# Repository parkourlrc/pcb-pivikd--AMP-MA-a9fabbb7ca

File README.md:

# Project Status

   **AMP-MA is currently in the early development phase and is considered unstable. The first stable release is scheduled for Q4 2026**
   
   **The project is currently in the pre-alpha stage – creating the first prototype**

# AMP-MA (AMP Modus Aequale)

AMP-MA (standing for Modus Aequale, signifying a rhythmic, ideal tone and modular structure) is an open-source, transistor-based guitar combo amplifier project. It is designed to bridge the gap between solid-state reliability and the organic, harmonic richness of vacuum tube sound.

The project focuses on a modular architecture, originally developed as a high-fidelity upgrade for the **Epiphone 15C** PCB. By utilizing independent blocks, AMP-MA allows for seamless customization and easier adaptation to various amp enclosures.

This project is designed and maintained by: [Danylo Pyvovarov](https://github.com/pivikd).

   1. [Key Features](#key-features)
   1. [Signal Chain](#signal-chain)
   1. [Integrated Tone Stacks](#integrated-tone-stacks)
<!-- 1. [Integrated Effects Modules](#integrated-effects-modules) -->
## Key Features
   - **Tube-like Architecture**: Uses **Mu-amp** based cascades with **2SK30A** transistors to achieve a warm, organic sound and harmonic saturation that mimics vacuum tube behavior.

   - **Dual Input Support**: Designed to handle two guitars simultaneously.

   - **Legendary Tone Stacks**: Features a 3-band EQ based on the classic tone stacks([Integrated Tone Stacks](#integrated-tone-stacks)).

   - **Integrated Compression**: Built-in compressor block based on the vintage **Ibanez CP835** circuitry.

   <!-- - **Modular Design**: Optimized for easy integration into different amp cabinets or for swapping internal effect modules. -->

## Signal Chain
   1. Input buffer
   1. Preamp ([Mu-AMP](https://www.muzique.com/amz/mini.htm))
   1. Compressor ([Ibanez CP835](https://www.scribd.com/document/976348354/Ibanez-CP835-Schematic))
   1. Tone Stack
   1. Recovery Stage
   1. Power Amp ([LM1875](https://www.ti.com/lit/ds/symlink/lm1875.pdf))

<!-- ## Integrated Effects Modules
|       Effect      |   based on   |  Status  |
|-------------------|--------------|---------|
| Compressor        | Ibanez CP835 |  done   |
<!-- | Over Drive        | Boss OD3     | planned  |
| Chorus            | Boss Ch1     | planned  | --> 

## Integrated Tone Stacks
   - Fender Treble-Middle-Bass
   - Marshall ([JCM900 2100 SL-X](https://stompboxelectronics.com/2023/12/16/the-marshall-tone-stacks/))
   - Dumble Rock

      Own:
   - TS0 (based on Marshall JCM900 2100 SL-x)
   - TS1 (based on Dumble Rock)

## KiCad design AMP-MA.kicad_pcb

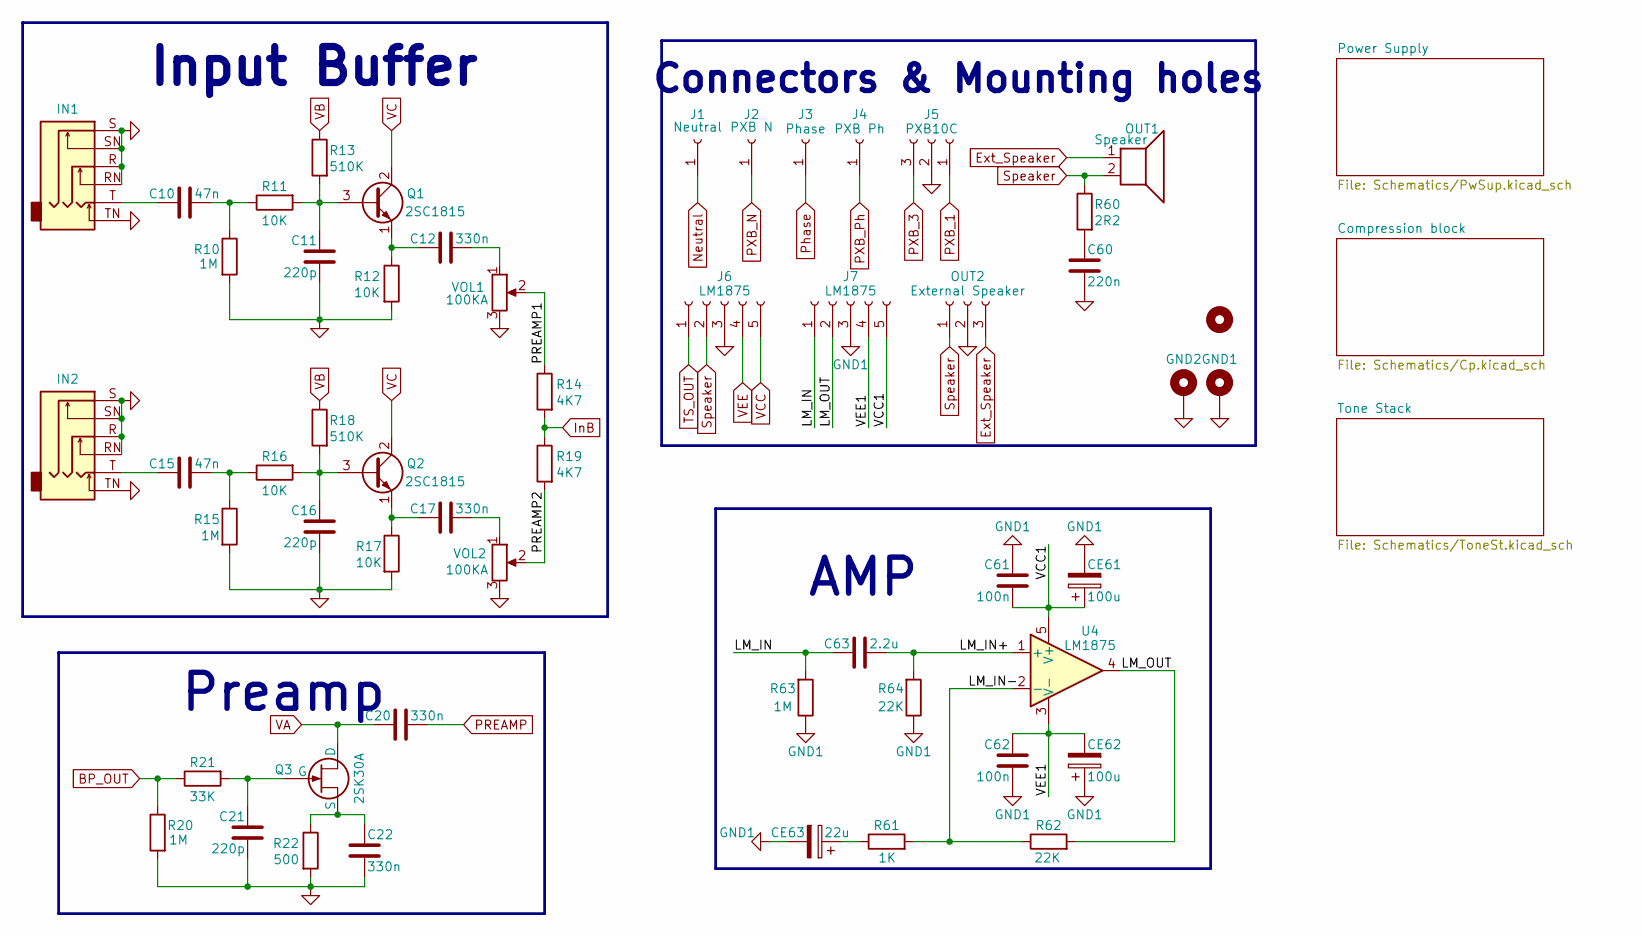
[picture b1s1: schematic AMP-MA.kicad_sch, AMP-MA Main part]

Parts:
C10, C15: 47n; C_disc_D7_W2.5_P5
C11, C16, C21: 220p; C_disc_D7_W2.5_P5
C12, C17, C20, C22: 330n; C_disc_D7_W2.5_P5
C60: 220n; C_disc_D7_W2.5_P5
C61, C62: 100n; C_disc_D7_W2.5_P5
C63: 2.2u; C_disc_D7_W2.5_P5
CE61, CE62: 100u; CP_Radial_D6.3mm_P2.50mm
CE63: 22u; CP_Radial_D5.0mm_P2.50mm
GND1, GND2: MountingHole_Pad; MountingHole_2.2mm_M2_DIN965_Pad
H2: MountingHole; MountingHole_2.2mm_M2
IN1, IN2: Jack_3_6pin
J1: Neutral; connector
J2: PXB N; connector
J3: Phase
J4: PXB Ph
J5: PXB10C; JST_XH_B3B-XH-A_1x03_P2.50mm_Vertical
J6, J7: LM1875; JST_XH_B5B-XH-A_1x05_P2.50mm_Vertical
OUT1: Speaker; PinSocket_1x02_P2.54mm_Vertical
OUT2: External Speaker; JST_XH_B3B-XH-A_1x03_P2.50mm_Vertical
Q1, Q2: 2SC1815; TO-92_Inline_Wide
Q3: 2SK30A; TO-92_Inline_Wide
R10, R15, R20, R63: 1M; R_Axial_DIN0207_L6.3mm_D2.5mm_P10.16mm_Horizontal
R11, R12, R16, R17: 10K; R_Axial_DIN0207_L6.3mm_D2.5mm_P10.16mm_Horizontal
R13, R18: 510K; R_Axial_DIN0207_L6.3mm_D2.5mm_P10.16mm_Horizontal
R14, R19: 4K7; R_Axial_DIN0207_L6.3mm_D2.5mm_P10.16mm_Horizontal
R21: 33K; R_Axial_DIN0207_L6.3mm_D2.5mm_P10.16mm_Horizontal
R22: 500; R_Axial_DIN0207_L6.3mm_D2.5mm_P10.16mm_Horizontal
R60: 2R2; R_Axial_DIN0207_L6.3mm_D2.5mm_P10.16mm_Horizontal
R61: 1K; R_Axial_DIN0207_L6.3mm_D2.5mm_P10.16mm_Horizontal
R62, R64: 22K; R_Axial_DIN0207_L6.3mm_D2.5mm_P10.16mm_Horizontal
U4: LM1875; TO-220-5_P3.4x3.7mm_StaggerOdd_Lead3.8mm_Vertical
VOL1, VOL2: 100KA; potentiometer

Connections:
/LM_IN: C63.1, J7.1, R63.2
/LM_IN+: C63.2, R64.2, U4.1 (+)
/LM_IN-: R61.2, R62.1, U4.2 (-)
/LM_OUT: J7.2, R62.2, U4.4
/PREAMP1: R14.1, VOL1.2
/PREAMP2: R19.2, VOL2.2
/VCC1: C61.2, CE61.1, J7.5, U4.5 (V+)
/VEE1: C62.1, CE62.2, J7.4, U4.3 (V-)
BP_OUT: R20.1, R21.1; also elsewhere on the board
Ext_Speaker: OUT1.1, OUT2.3
GND: C11.1, C16.1, C21.1, C22.1, C60.2, GND1.1 (1_1), GND2.1 (1_1), IN1.R, IN1.RN, IN1.S, IN1.SN, IN1.TN, IN2.R, IN2.RN, IN2.S, IN2.SN, IN2.TN, J5.2, J6.3, OUT2.2, R10.2, R12.2, R15.2, R17.2, R20.2, R22.2, VOL1.3, VOL2.3; also elsewhere on the board
GND1: C61.1, C62.2, CE61.2, CE62.1, CE63.2, J7.3, R63.1, R64.1
InB: R14.2, R19.1; also elsewhere on the board
unnamed: C10.1, IN1.T
unnamed: C10.2, R10.1, R11.1
unnamed: C12.2, VOL1.1
unnamed: C15.1, IN2.T
unnamed: C15.2, R15.1, R16.1
unnamed: C17.2, VOL2.1
unnamed: C60.1, R60.2
unnamed: CE63.1, R61.1
unnamed: C11.2, Q1.3 (B), R11.2, R13.2
unnamed: C12.1, Q1.1 (E), R12.1
unnamed: C16.2, Q2.3 (B), R16.2, R18.2
unnamed: C17.1, Q2.1 (E), R17.1
unnamed: C21.2, Q3.2 (G), R21.2
unnamed: C22.2, Q3.3 (S), R22.1
Neutral: J1.1 (Pin_1_1); also elsewhere on the board
PREAMP: C20.2; also elsewhere on the board
PXB_1: J5.1; also elsewhere on the board
PXB_3: J5.3; also elsewhere on the board
PXB_N: J2.1 (Pin_1_1); also elsewhere on the board
Speaker: J6.2, OUT1.2, OUT2.1, R60.1
TS_OUT: J6.1; also elsewhere on the board
VA: C20.1, Q3.1 (D); also elsewhere on the board
VB: R13.1, R18.1; also elsewhere on the board
VC: Q1.2 (C), Q2.2 (C); also elsewhere on the board
VCC: J6.5; also elsewhere on the board
VEE: J6.4; also elsewhere on the board

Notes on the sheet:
Preamp
Connectors & Mounting holes
AMP
Input Buffer

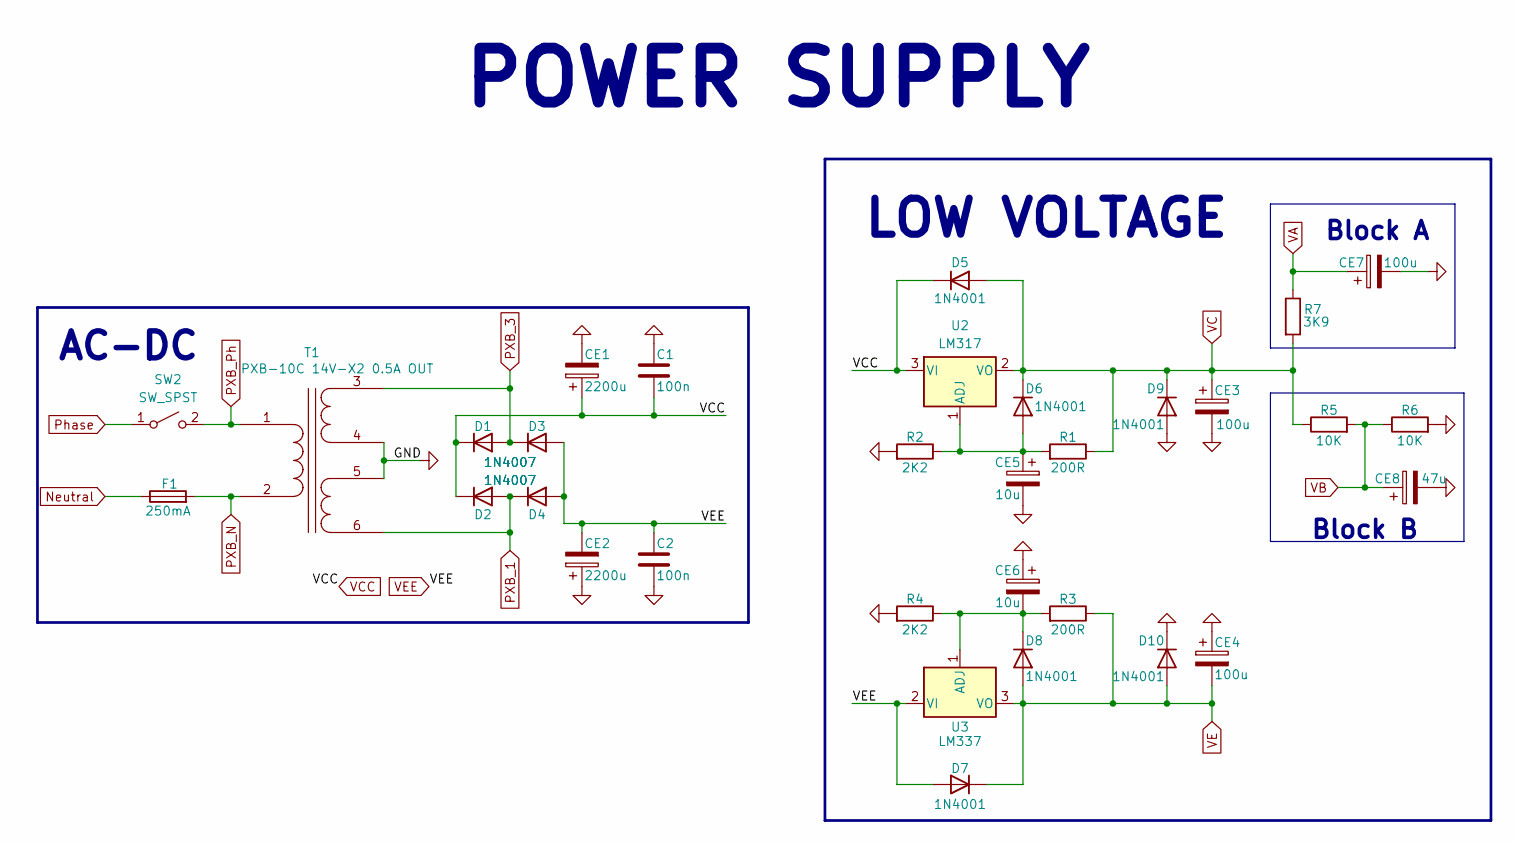
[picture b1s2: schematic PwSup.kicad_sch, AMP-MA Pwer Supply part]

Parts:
C1, C2: 100n; C_disc_D7_W2.5_P5
CE1, CE2: 2200u; CP_Radial_D16.0mm_P7.50mm
CE3, CE4, CE7: 100u; CP_Radial_D6.3mm_P2.50mm
CE5, CE6: 10u; CP_Radial_D5.0mm_P2.50mm
CE8: 47u; CP_Radial_D5.0mm_P2.50mm
D1, D2, D3, D4: 1N4007; D_DO-41_SOD81_P10.16mm_Horizontal
D5, D6, D7, D8, D9, D10: 1N4001; D_DO-41_SOD81_P10.16mm_Horizontal
F1: 250mA; Fuseholder_Clip-5x20mm_Littelfuse_520_Inline_P20.50x5.80mm_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
R1, R3: 200R; R_Axial_DIN0207_L6.3mm_D2.5mm_P10.16mm_Horizontal
R2, R4: 2K2; R_Axial_DIN0207_L6.3mm_D2.5mm_P10.16mm_Horizontal
R5, R6: 10K; R_Axial_DIN0207_L6.3mm_D2.5mm_P10.16mm_Horizontal
R7: 3K9; R_Axial_DIN0207_L6.3mm_D2.5mm_P10.16mm_Horizontal
SW2: SW_SPST
T1: PXB-10C 14V-X2 0.5A OUT
U2: LM317; TO-220-3_Horizontal_TabDown
U3: LM337; TO-220-3_Horizontal_TabDown

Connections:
GND: C1.2, C2.2, CE1.2, CE2.1, CE3.2, CE4.1, CE5.2, CE6.1, CE7.2, CE8.2, D9.2 (A), D10.1 (K), R2.2, R4.2, R6.2, T1.4 (SB), T1.5 (SC); also elsewhere on the board
unnamed: CE5.1, D6.2 (A), R1.2, R2.1, U2.1 (ADJ)
unnamed: CE6.2, D8.1 (K), R3.2, R4.1, U3.1 (ADJ)
unnamed: SW2.2 (B), T1.1 (AA)
Neutral: F1.1; also elsewhere on the board
PXB_1: D2.2 (A), D4.1 (K), T1.6 (SD); also elsewhere on the board
PXB_3: D1.2 (A), D3.1 (K), T1.3 (SA); also elsewhere on the board
PXB_N: F1.2, T1.2 (AB); also elsewhere on the board
VA: CE7.1, R7.1; also elsewhere on the board
VB: CE8.1, R5.2, R6.1; also elsewhere on the board
VC: CE3.1, D5.2 (A), D6.1 (K), D9.1 (K), R1.1, R5.1, R7.2, U2.2 (VO); also elsewhere on the board
VCC: C1.1, CE1.1, D1.1 (K), D2.1 (K), D5.1 (K), U2.3 (VI); also elsewhere on the board
VE: CE4.2, D7.1 (K), D8.2 (A), D10.2 (A), R3.1, U3.3 (VO); also elsewhere on the board
VEE: C2.1, CE2.2, D3.2 (A), D4.2 (A), D7.2 (A), U3.2 (VI); also elsewhere on the board

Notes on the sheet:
AC-DC
Block A
Block B
LOW VOLTAGE
POWER SUPPLY

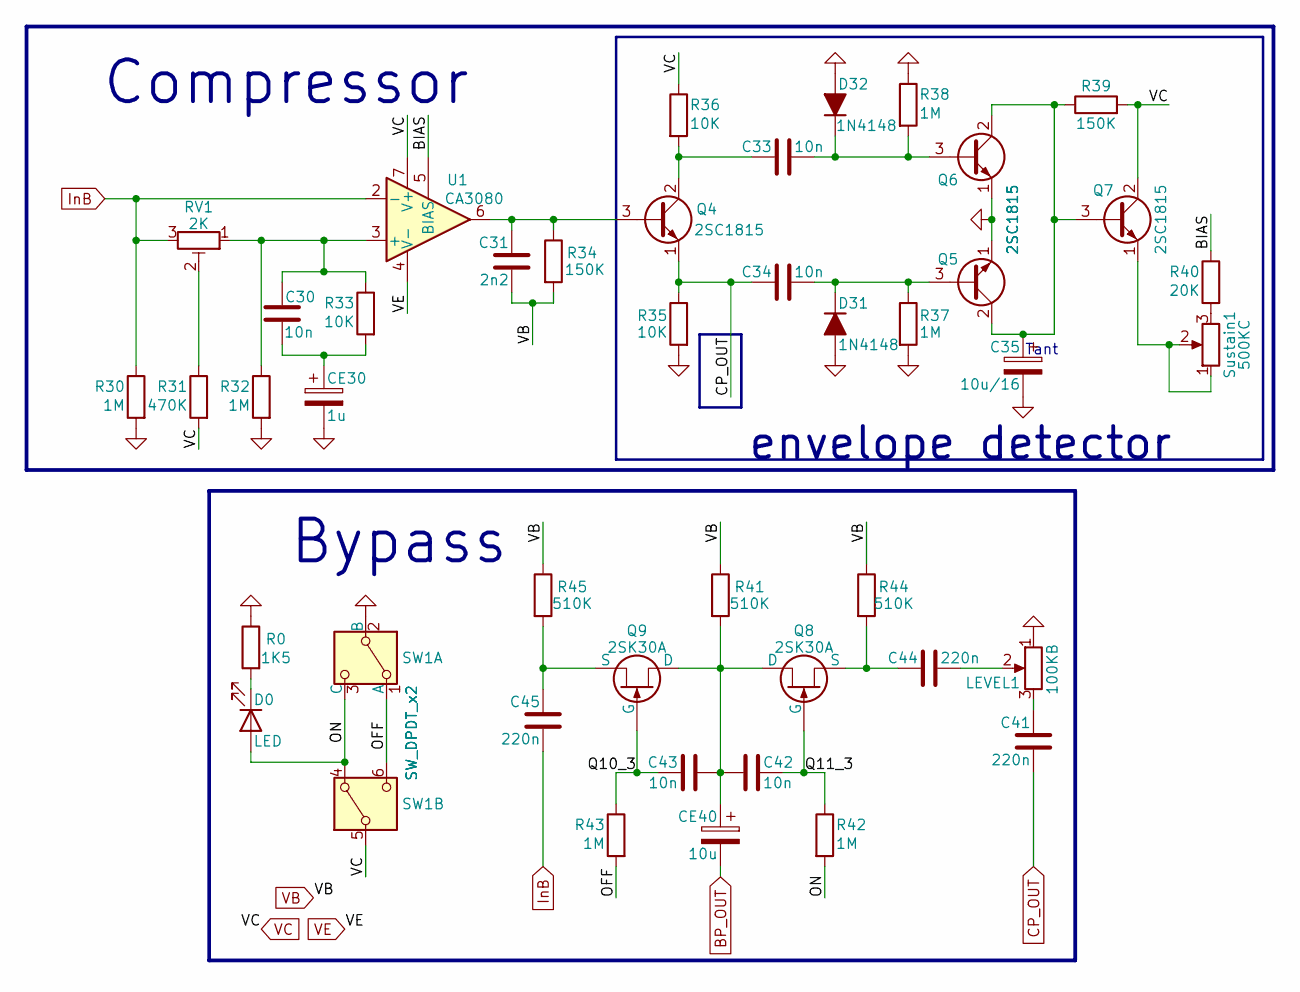
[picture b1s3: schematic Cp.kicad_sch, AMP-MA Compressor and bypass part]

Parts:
C30: 10n; C_disc_D7_W2.5_P5
C31: 2n2; C_Disc_D4.3_W1.9_P5.00
C33, C34, C42, C43: 10n; C_Disc_D4.3_W1.9_P5.00
C35: 10u/16; CP_Radial_Tantal_D5.5mm_P2.50mm
C41, C44, C45: 220n; C_disc_D7_W2.5_P5
CE30: 1u; CP_Radial_D4.0mm_P2.00mm
CE40: 10u; CP_Radial_D5.0mm_P2.50mm
D0: LED; LED_D3.0mm_Horizontal_O6.35mm_Z6.0mm
D31, D32: 1N4148; D_DO-35_SOD27_P7.62mm_Horizontal
LEVEL1: 100KB; Potentiometer_Bourns_3296W_Vertical
Q4, Q5, Q6, Q7: 2SC1815; TO-92_Inline_Wide
Q8, Q9: 2SK30A; TO-92_Inline_Wide
R0: 1K5; R_Axial_DIN0207_L6.3mm_D2.5mm_P10.16mm_Horizontal
R30, R32, R37, R38, R42, R43: 1M; R_Axial_DIN0207_L6.3mm_D2.5mm_P10.16mm_Horizontal
R31: 470K; R_Axial_DIN0207_L6.3mm_D2.5mm_P10.16mm_Horizontal
R33, R35, R36: 10K; R_Axial_DIN0207_L6.3mm_D2.5mm_P10.16mm_Horizontal
R34, R39: 150K; R_Axial_DIN0207_L6.3mm_D2.5mm_P10.16mm_Horizontal
R40: 20K; R_Axial_DIN0207_L6.3mm_D2.5mm_P10.16mm_Horizontal
R41, R44, R45: 510K; R_Axial_DIN0207_L6.3mm_D2.5mm_P10.16mm_Horizontal
RV1: 2K; Potentiometer_Bourns_3296W_Vertical
SW1: SW_DPDT_x2; SW DPDT
Sustain1: 500KC; potentiometer
U1: CA3080; DIP-8_W7.62mm

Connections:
/Compression block/BIAS: R40.1, U1.5 (BIAS)
/Compression block/OFF: R43.2, SW1.1 (A), SW1.6 (C)
/Compression block/ON: D0.2 (A), R42.2, SW1.3 (C), SW1.4 (A)
/Compression block/Q10_3: C43.2, Q9.2 (G), R43.1
/Compression block/Q11_3: C42.1, Q8.2 (G), R42.1
BP_OUT: CE40.2; also elsewhere on the board
CP_OUT: C34.1, C41.1, Q4.1 (E), R35.1
GND: C35.2, CE30.2, D31.2 (A), D32.2 (A), LEVEL1.1, Q5.1 (E), Q6.1 (E), R0.1, R30.2, R32.2, R35.2, R37.2, R38.1, SW1.2 (B); also elsewhere on the board
InB: C45.1, R30.1, RV1.3, U1.2 (-); also elsewhere on the board
unnamed: C30.2, CE30.1, R33.2
unnamed: C41.2, LEVEL1.3
unnamed: C44.2, LEVEL1.2
unnamed: D0.1 (K), R0.2
unnamed: C34.2, D31.1 (K), Q5.3 (B), R37.1
unnamed: C33.2, D32.1 (K), Q6.3 (B), R38.2
unnamed: C31.1, Q4.3 (B), R34.1, U1.6
unnamed: C33.1, Q4.2 (C), R36.2
unnamed: C35.1, Q5.2 (C), Q6.2 (C), Q7.3 (B), R39.1
unnamed: Q7.1 (E), Sustain1.1, Sustain1.2
unnamed: C42.2, C43.1, CE40.1, Q8.1 (D), Q9.1 (D), R41.2
unnamed: C44.1, Q8.3 (S), R44.2
unnamed: C45.2, Q9.3 (S), R45.2
unnamed: R31.1, RV1.2
unnamed: R40.2, Sustain1.3
unnamed: C30.1, R32.1, R33.1, RV1.1, U1.3 (+)
VB: C31.2, R34.2, R41.1, R44.1, R45.1; also elsewhere on the board
VC: Q7.2 (C), R31.2, R36.1, R39.2, SW1.5 (B), U1.7 (V+); also elsewhere on the board
VE: U1.4 (V-); also elsewhere on the board

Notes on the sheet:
Bypass
envelope detector
Tant
Compressor

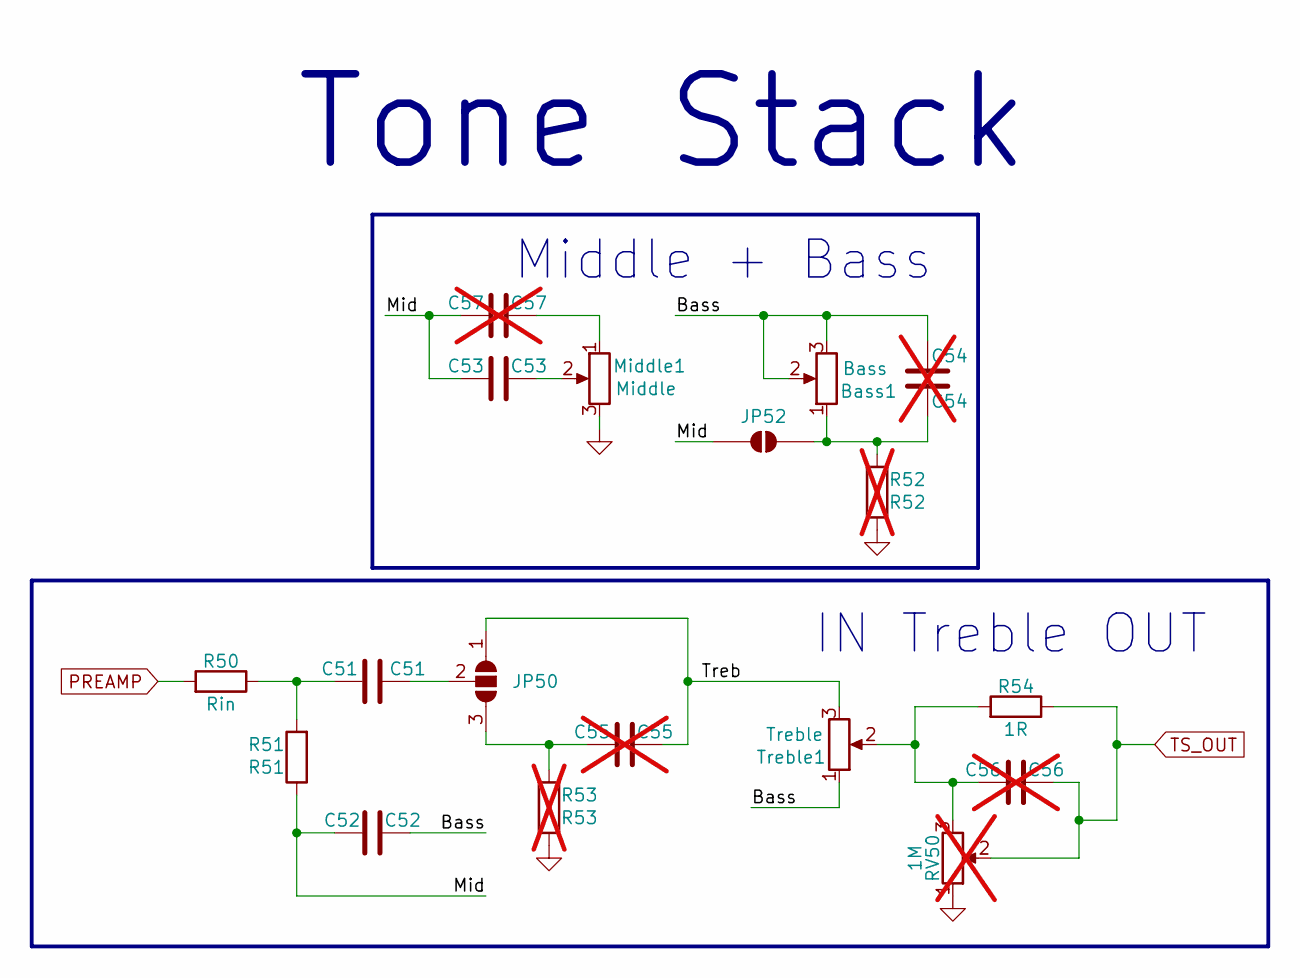
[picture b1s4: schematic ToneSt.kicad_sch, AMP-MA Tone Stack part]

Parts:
Bass1: Bass; potentiometer
C51: C51; C_disc_D7_W2.5_P5
C52: C52; C_disc_D7_W2.5_P5
C53: C53; C_disc_D7_W2.5_P5
C54: C54; C_disc_D7_W2.5_P5; not fitted
C55: C55; C_disc_D7_W2.5_P5; not fitted
C56: C56; C_disc_D7_W2.5_P5; not fitted
C57: C57; C_disc_D7_W2.5_P5; not fitted
JP50: SolderJumper_3_Open; SolderJumper-3_P2.0mm_Open_TrianglePad1.0x1.5mm_NumberLabels
JP52: SolderJumper_2_Open; SolderJumper-2_P1.3mm_Open_TrianglePad1.0x1.5mm
Middle1: Middle; potentiometer
R50: Rin; R_Axial_DIN0207_L6.3mm_D2.5mm_P10.16mm_Horizontal
R51: R51; R_Axial_DIN0207_L6.3mm_D2.5mm_P10.16mm_Horizontal
R52: R52; R_Axial_DIN0207_L6.3mm_D2.5mm_P10.16mm_Horizontal; not fitted
R53: R53; R_Axial_DIN0207_L6.3mm_D2.5mm_P10.16mm_Horizontal; not fitted
R54: 1R; R_Axial_DIN0207_L6.3mm_D2.5mm_P10.16mm_Horizontal
RV50: 1M; Potentiometer_Bourns_3296W_Vertical; not fitted
Treble1: Treble; potentiometer

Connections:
/Tone Stack/Bass: Bass1.2, Bass1.3, C52.2, C54.2, Treble1.1
/Tone Stack/Mid: C52.1, C53.1, C57.1, JP52.1 (A), R51.1
/Tone Stack/Treb: C55.2, JP50.1 (A), Treble1.3
GND: Middle1.3, R52.1, R53.1, RV50.1; also elsewhere on the board
unnamed: C51.1, R50.1, R51.2
unnamed: C53.2, Middle1.2
unnamed: C56.1, R54.2, RV50.3, Treble1.2
unnamed: C57.2, Middle1.1
unnamed: C55.1, JP50.3 (B), R53.2
unnamed: C51.2, JP50.2 (C)
unnamed: Bass1.1, C54.1, JP52.2 (B), R52.2
PREAMP: R50.2; also elsewhere on the board
TS_OUT: C56.2, R54.1, RV50.2; also elsewhere on the board

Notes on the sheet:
Tone Stack
Middle + Bass
IN Treble OUT

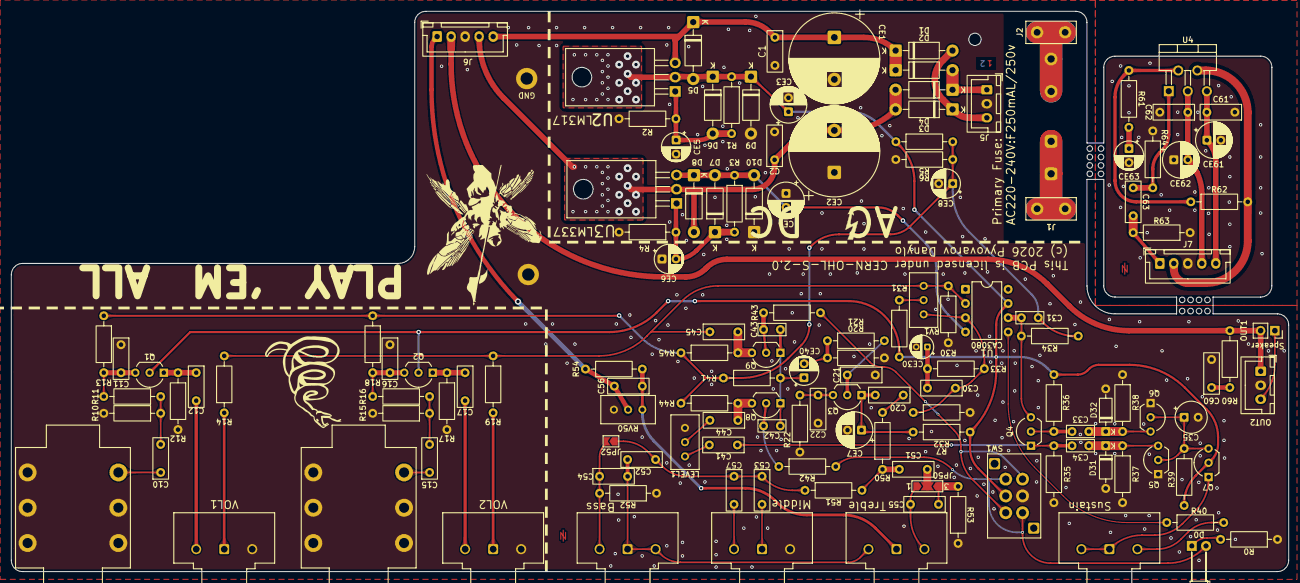
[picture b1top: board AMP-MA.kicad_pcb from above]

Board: 2 copper layers, 228.0 x 100.0 mm, 143 parts (1 on the bottom side), 74 nets.

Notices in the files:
AMP-MA.kicad_pcb:
Copyright (c) 2026 Pyvovarov Dannylo
License: CERN-OHL-S-2.0
This PCB is licensed under CERN-OHL-S-2.0
(c) 2026 Pyvovarov Danylo
README.md:
License: GPL-3.0
